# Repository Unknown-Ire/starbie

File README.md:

# Starbie — routed PCB for review

Starbie is a beginner electronics project based on the [Starbie Week 1 guide](https://github.com/SharKingStudios/Starbie/blob/main/Week%201%20Guide.md). It combines a Seeed XIAO ESP32-C3, two buttons, an OLED display connection, a motion-sensor connection and a DHT11 temperature/humidity sensor.

## Current status — 16 November 2026

- Full schematic and seven physical component footprints included.
- 70 × 75 mm rounded board with USB access at its top edge.
- All 20 previously outstanding connections routed on two copper layers.
- 0.30 mm tracks; 10 through vias, 0.60 mm diameter / 0.30 mm drill.
- KiCad 10 DRC: **0 violations, 0 unconnected items, 0 schematic parity issues**. The JSON report is in `checks/`.
- Gerber and plated/non-plated drill files exported into `manufacturing_review/`.
- No hardware has been assembled, powered or tested. Firmware is not implemented in this package.

This is a routed review version, not an authorization to order. Exact purchased module dimensions, pin order and assembly method still need checking. A clean DRC confirms consistency with the digital design rules; it does not prove that a selected module fits or that the physical device works. The routing includes vias near/within controller pads, which should be reviewed for the intended soldering method before manufacture.

## Opening the project

Extract the entire folder and open `Starbie.kicad_pro` in KiCad 10. Keep the `Week 1 Care Package` folder beside the project files: the symbol and footprint libraries use project-relative paths. Open the PCB Editor to see the new copper routing. The earlier placement-only project remains a separate copy.

Red tracks are front copper; blue tracks are back copper. Vias are plated holes connecting the two sides. No ground pour has been added; ground is connected using tracks.

The schematic below shows how the controller, buttons, display and sensors connect.

## Connections for eventual firmware

| Function | XIAO label | ESP32-C3 GPIO |
|---|---|---|
| OLED / MPU6050 SDA | D5 | GPIO7 |
| OLED / MPU6050 SCL | D4 | GPIO6 |
| DHT11 DATA | D1 | GPIO3 |
| Button SW1 | D2 | GPIO4 |
| Button SW2 | D3 | GPIO5 |

The I²C assignment is deliberately explicit: eventual firmware should initialize SDA on GPIO7 and SCL on GPIO6. Both buttons connect to GND when pressed and require the corresponding input pull-ups in firmware. MPU6050 AD0 is tied to GND; check address 0x68 when testing. R1 is a 10 kΩ pull-up from DHT_DATA to 3V3. Power is intended through the XIAO's USB connector; VBAT and VBUS pads are not connected on this carrier board.

## Draft bill of materials

These are candidate parts and listed prices from the sourcing comparison, not a completed funding budget. Prices below are in **GBP**, as listed by the suppliers. The dashboard requires the final purchase prices in **USD**, including tax and delivery.

| Reference | Part | Quantity to buy | Unit price (GBP) | Buying link |
|---|---|---:|---|---|
| U1 | Seeed XIAO ESP32-C3, board with loose headers | 1 | £5.40 | [The Pi Hut](https://thepihut.com/products/seeed-xiao-esp32c3) |
| J1 | HCMODU0164 SSD1306 0.96-inch I²C OLED | 1 | £3.33 excluding VAT | [Hobby Components](https://hobbycomponents.com/displays/1160-096-i2c-iic-oled-module) |
| J2 | ST071 GY-521 / MPU6050 module | 1 | From £3.27; confirm variant | [Bitsbox](https://www.bitsboxuk.com/index.php?main_page=product_info&products_id=3059) |
| U2 | ST092 bare four-pin DHT11 | 1 | £1.85 | [Bitsbox](https://www.bitsboxuk.com/index.php?main_page=product_info&products_id=3679) |
| SW1, SW2 | CHERRY MX1A-G1NW PCB-mount brown switch | 2 | £0.48 | [Keyboard Company](https://www.keyboardco.com/product/cherry-key-switch-module-brown-tactile-pcb-mount.asp) |
| R1 | MR2510K 10 kΩ axial resistor | 10 minimum; fit one | £0.06 | [Bitsbox](https://www.bitsboxuk.com/index.php?cPath=83_88&main_page=product_info&products_id=594) |
| Headers | CN344 40-way 2.54 mm header strip | 1 strip | £0.24 | [Bitsbox](https://www.bitsboxuk.com/index.php?cPath=225_230&main_page=product_info&products_id=2409) |
| PCB | Custom two-layer 70 × 75 mm board | Manufacturer's minimum batch | Quote required | [JLCPCB quotation](https://jlcpcb.com/) |

The listed GBP component subtotal is **£15.65**, excluding OLED VAT, PCB fabrication and delivery. The [BOM.csv](BOM.csv) now contains a **USD planning draft**: $25.57 for parts and the PCB batch, plus $13.77 in known/estimated delivery, for **$39.34 before two other supplier delivery charges and remaining adjustments**. This exceeds the dashboard's $30 Tier 1 limit and is not ready for funding submission. The OLED's USD estimate includes a 20% UK VAT allowance; do not count it twice. See [SOURCING.md](SOURCING.md) for the conversion, PCB calculator evidence and missing costs. Use **Import from repo** on the dashboard to load the draft rows. Tools are handled separately by the programme's shop.

## Imported component models

The bundled STEP files are reference models of purchased components from the tutorial care package. They are not a custom enclosure designed for this project. The editable PCB and schematic sources are the included KiCad files. No original Fusion or Onshape enclosure model is claimed here.

## Remaining work

1. Select exact compatible parts and confirm their documentation, dimensions and connector order.
2. Review soldering access, module clearances, USB access and any enclosure needs.
3. Recheck/export if any footprint or placement changes are needed.
4. Prepare a real priced BOM within the approved budget and publish the project repository.
5. Document the participant's active work and the help used; submit through the programme's checklist.
6. After approval, assemble and test the hardware, then implement and test firmware.

## Attribution

Based on SharKingStudios' Starbie tutorial. Schematic completion, footprint corrections, component placement, PCB routing, checks, exports and documentation.

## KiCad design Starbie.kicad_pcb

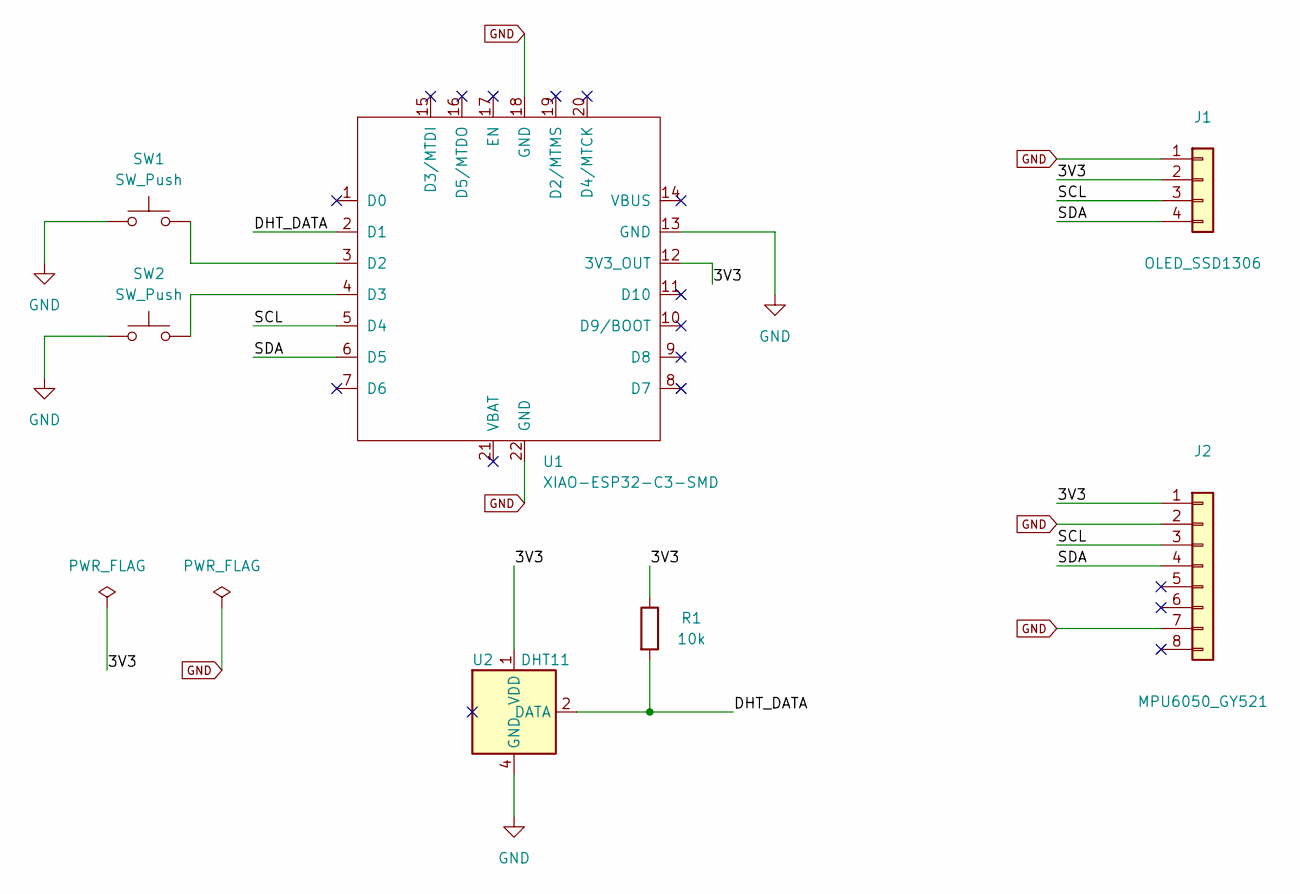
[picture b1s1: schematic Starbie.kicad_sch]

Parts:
J1: OLED_SSD1306; Display_128x64_096_I2C
J2: MPU6050_GY521; MPU6050_Module
R1: 10k; R_Axial_DIN0207_L6.3mm_D2.5mm_P7.62mm_Horizontal
SW1, SW2: SW_Push; SW_Cherry_MX_1.00u_PCB
U1: XIAO-ESP32-C3-SMD
U2: DHT11; Aosong_DHT11_5.5x12.0_P2.54mm

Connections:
/3V3: J1.2, J2.1, R1.1, U1.12 (3V3_OUT), U2.1 (VDD)
/DHT_DATA: R1.2, U1.2 (D1), U2.2 (DATA)
/SCL: J1.3, J2.3, U1.5 (D4)
/SDA: J1.4, J2.4, U1.6 (D5)
GND: J1.1, J2.2, J2.7, SW1.1, SW2.1, U1.13 (GND), U1.18 (GND), U1.22 (GND), U2.4 (GND)
unnamed: SW1.2, U1.3 (D2)
unnamed: SW2.2, U1.4 (D3)

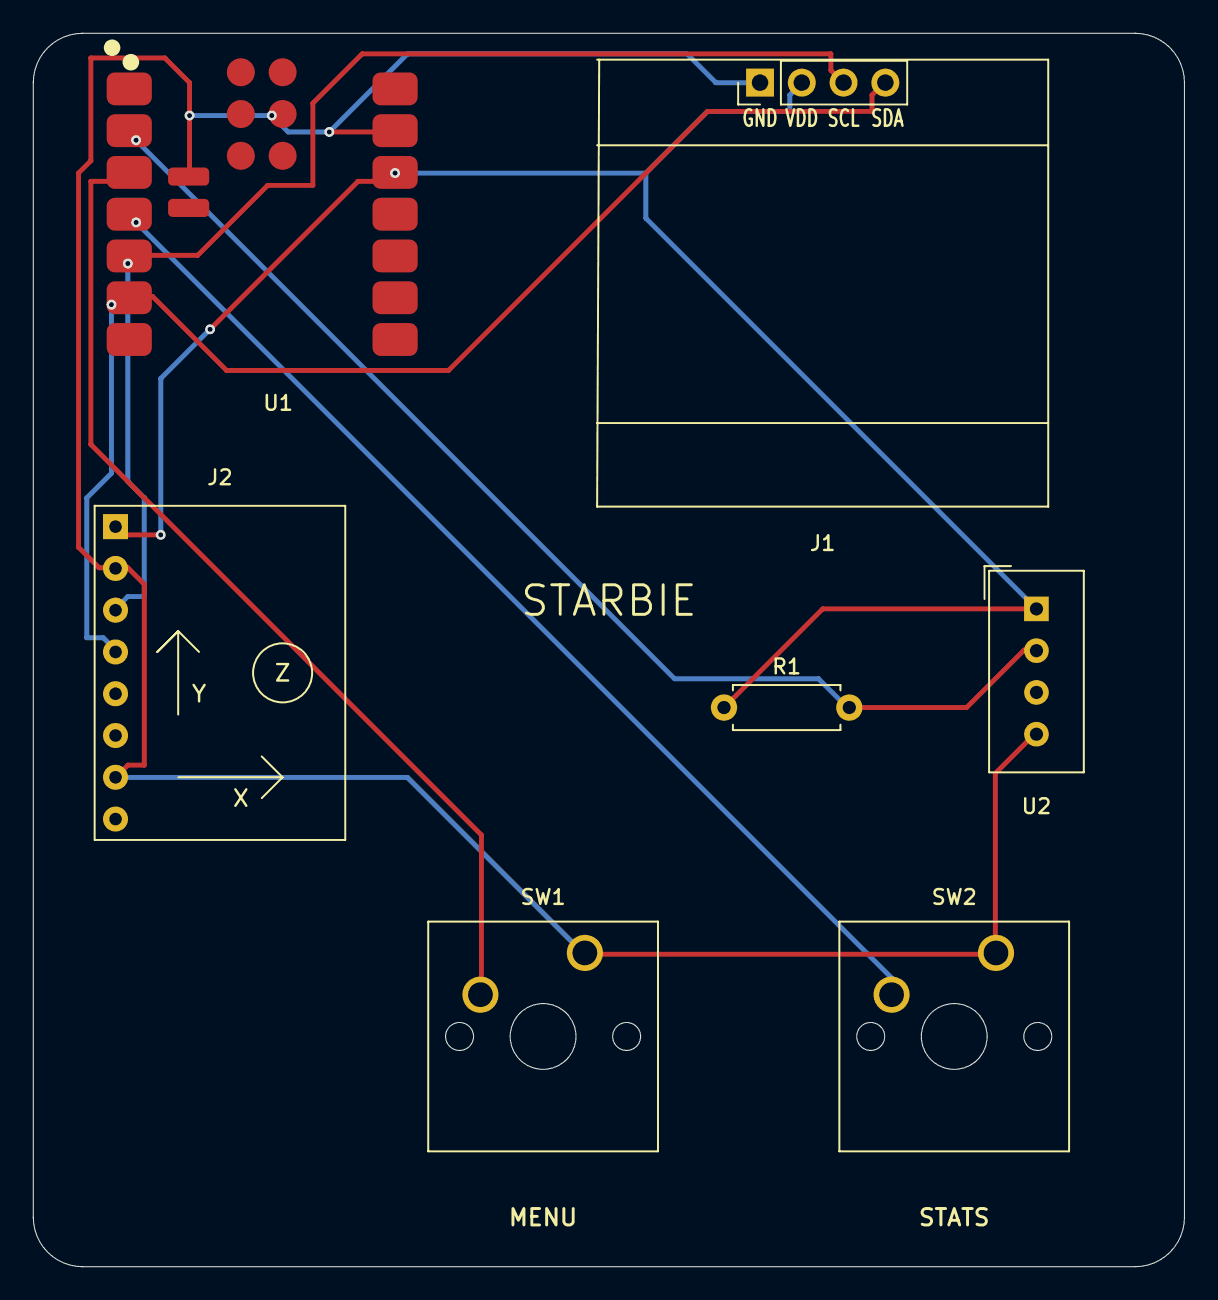
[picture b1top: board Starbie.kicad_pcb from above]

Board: 2 copper layers, 70.0 x 75.0 mm, 7 parts (0 on the bottom side), 7 nets.
